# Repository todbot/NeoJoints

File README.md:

# NeoJoints
Neopixel Joints, millable on the Othermill

Table of Contents
=================

  * [What are these?](#what-are-these)
  * [Available NeoJoints](#available-neojoints)
  * [How to Solder](#how-to-solder)

## What are these?
NeoJoints make it easy to solder together pieces of WS2812 / NeoPixel-style
LED strip.

NeoJoints have the following features
* Available in multiple angles
* Solderable holes for adding additional power at joints
* Cuttable trace on data line for separating strips logically
* Mounting hole for 2-56 screw
* Single-sided millable on PCB mill like Othermill,
    with a single 1/32" endmill (though adding 1/8" to cleanup helps)

Originally from 5 Jun 2015 task for "Mill-a-Week": https://github.com/todbot/Mill-a-Week

## Available NeoJoints

* **NeoJointV2-090**
    - 90-degree right angle

* **NeoJointV2-000**
    - 0-degree straight joint

* **NeoJointV2-060**
    - 60-degree joint  (good for making triangles)

* **NeoJointV2-120**
    - 120-degree joint (good for making hexagons)

* **NeoJointV2-082p43**
    - 82.43-degree angle, for inner angle of 7-segment-style display

* **NeoJointV2-097p57**
    - 97.57-degree angle, for outer angle of 7-segment-style display

* **NeoJointV2-180-10mm**
    - 180-degree angle, for putting serpentining strips

* **NeoJointV2-180-20mm**
    - 180-degree angle, for putting serpentining strips

* more coming...

## How to Solder

* Step 1: Get NeoJoint and LED strip pieces laid out correctly
  - Be sure to make sure data arrows are pointing correctly

* Step 2: Turn over strips, put small solder blobs on *back* of each pad
  - Depending on the strip, you may need to scratch away adhesive layer or waterproofing

* Step 3: Lay strip on top of NeoJoint, then heat up with soldering iron to melt solder blobs, one by one
  - Take care to keep strip aligned when melting first solder blob

* Step 4: Continue until you've soldered down all points
  - You can look along the side of the strip to see if the solder has melted
  - And you can see if you have any solder bridges

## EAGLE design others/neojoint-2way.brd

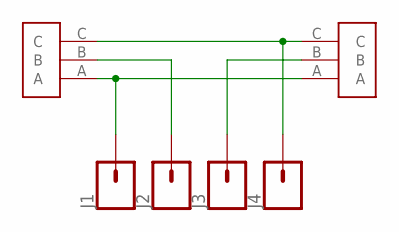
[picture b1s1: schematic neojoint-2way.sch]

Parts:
J1, J2, J3, J4: CONN_01; 1X01
U$1, U$2: LED_STRIP_3P; LEDSTRIP-3P

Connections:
unnamed: J1.1, U$1.A, U$2.A
unnamed: J2.1, U$2.B
unnamed: J4.1, U$1.C, U$2.C
unnamed: J3.1, U$1.B

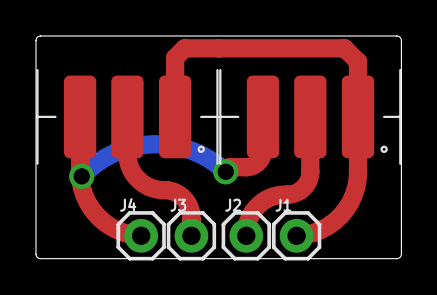
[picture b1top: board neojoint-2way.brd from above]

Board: 2 copper layers, 20.3 x 12.4 mm, 6 parts (0 on the bottom side), 4 nets.

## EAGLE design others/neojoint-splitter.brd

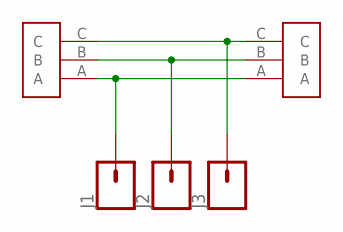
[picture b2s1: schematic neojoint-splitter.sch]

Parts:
J1, J2, J3: CONN_01; 1X01
U$1, U$2: LED_STRIP_3P; LEDSTRIP-3P

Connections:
unnamed: J1.1, U$1.A, U$2.A
unnamed: J2.1, U$1.B, U$2.B
unnamed: J3.1, U$1.C, U$2.C

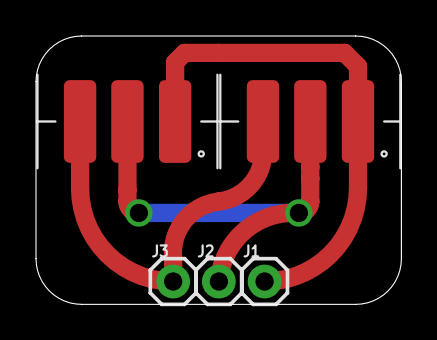
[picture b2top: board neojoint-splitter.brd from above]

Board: 2 copper layers, 20.3 x 14.9 mm, 5 parts (0 on the bottom side), 3 nets.

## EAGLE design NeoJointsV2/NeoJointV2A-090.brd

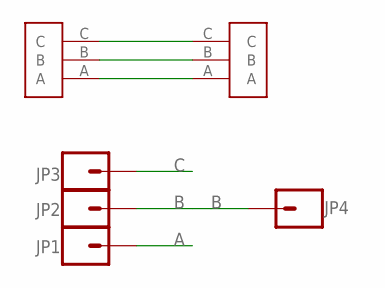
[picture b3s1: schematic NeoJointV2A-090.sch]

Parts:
JP1, JP2, JP3, JP4: M01PTH; 1X01
U$1, U$2: LED_STRIP_3P; LEDSTRIP-3P

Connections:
A: JP1.1, U$1.A, U$2.A
B: JP2.1, JP4.1, U$1.B, U$2.B
C: JP3.1, U$1.C, U$2.C

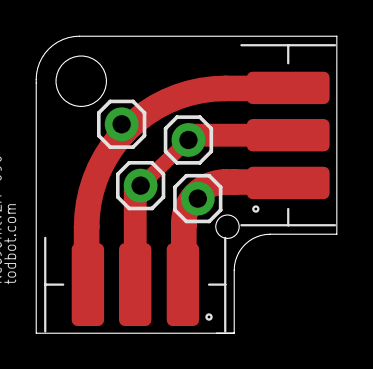
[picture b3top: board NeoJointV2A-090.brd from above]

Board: 2 copper layers, 16.7 x 16.5 mm, 6 parts (0 on the bottom side), 3 nets.

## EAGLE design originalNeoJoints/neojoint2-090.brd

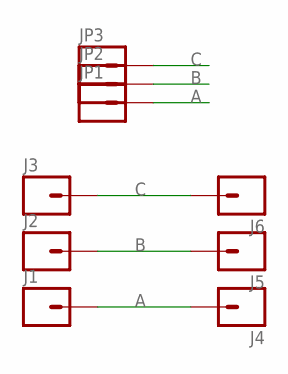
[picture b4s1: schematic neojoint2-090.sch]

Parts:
J1, J2, J3, J4, J5, J6: M01SMD-4.5X1.5; PAD-1.5X4.5
JP1, JP2, JP3: M01PTH; 1X01

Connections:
A: J1.P$1, J4.P$1, JP1.1
B: J2.P$1, J5.P$1, JP2.1
C: J3.P$1, J6.P$1, JP3.1

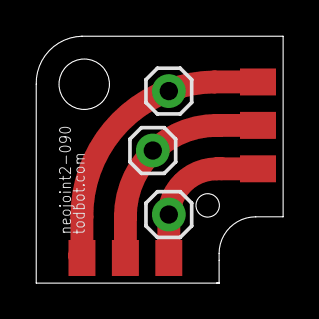
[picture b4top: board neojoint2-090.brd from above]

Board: 2 copper layers, 13.7 x 13.7 mm, 9 parts (0 on the bottom side), 3 nets.

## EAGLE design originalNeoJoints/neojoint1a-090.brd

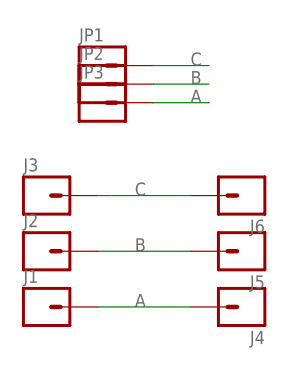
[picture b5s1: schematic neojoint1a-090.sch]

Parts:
J1, J2, J3, J4, J5, J6: M01SMD-4.5X1.5; PAD-1.5X4.5
JP1, JP2, JP3: M01PTH; 1X01

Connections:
A: J1.P$1, J4.P$1, JP3.1
B: J2.P$1, J5.P$1, JP2.1
C: J3.P$1, J6.P$1, JP1.1

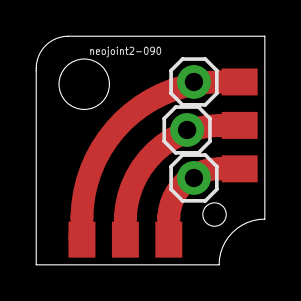
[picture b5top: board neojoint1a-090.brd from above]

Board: 2 copper layers, 12.7 x 12.7 mm, 9 parts (0 on the bottom side), 3 nets.

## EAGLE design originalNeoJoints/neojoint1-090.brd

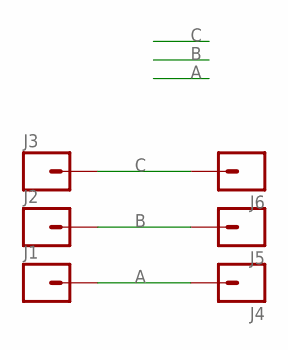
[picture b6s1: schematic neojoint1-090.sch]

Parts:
J1, J2, J3, J4, J5, J6: M01SMD-4.5X1.5; PAD-1.5X4.5

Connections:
A: J1.P$1, J4.P$1
B: J2.P$1, J5.P$1
C: J3.P$1, J6.P$1

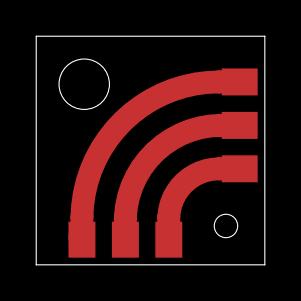
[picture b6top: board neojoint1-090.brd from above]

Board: 2 copper layers, 12.7 x 12.7 mm, 6 parts (0 on the bottom side), 3 nets.

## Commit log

2017-02-23 first
2017-02-23 moved over to new place
2017-02-23 first add of v2 style
2017-02-24 update neojointv2a
2017-02-24 added first cut of Eagle library
2017-02-24 first add of NeoJoint 82.43 degrees, for seven-segment like displays for @johnedgarpark
2017-02-24 fix inner radius a bit on 82p43
2017-02-24 first add of NeoJoint 97.57 degrees, for seven-segment like displays for @johnedgarpark
2017-02-24 small cleanup and added images
2017-02-24 added docs
2017-02-25 added more docs
2017-02-25 added 180 variant
2017-02-25 fix doc
2017-02-25 update doc
2017-02-25 rename 180 to 000 since it is a straight, not a u-turn
2017-02-26 layout fixes for 000,090,120
2017-03-11 added a bunch of new types
2017-03-11 added img
2017-03-15 added 60 degree
2017-03-16 added splitter from ilovelamp
2017-03-17 added 30mm wide splitter
2017-03-31 added neojoint-2way
2017-04-21 added 180 degree 10mm
2017-06-12 added 180-degree variants

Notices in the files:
parts and their libraries:
SparkFun-Connectors: Licensing: Creative Commons ShareAlike 4.0 International - https://creativecommons.org/licenses/by-sa/4.0
